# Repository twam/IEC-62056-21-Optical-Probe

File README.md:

IEC-62056-21-Optical-Probe
===

Optical probe for reading out power meters supporting the [IEC 62056-21](https://www.ungelesen.net/protagWork/media/downloads/solar-steuerung/iec62056-21%7Bed1.0%7Den_.pdf) standard via USB.

Infrared part is based on https://wiki.volkszaehler.org/hardware/controllers/ir-schreib-lesekopf-ttl-ausgang.

For the case a ring magnet with Ø 26,75/16 mm and 5 mm height is required, e.g. [this one](https://www.supermagnete.de/eng/ring-magnets-neodymium/ring-magnet-26.75mm-16mm-5mm_R-27-16-05-N).

### JLCPCB

PCBs can be ordered fully-assembled (besides the IR-LED and Photodiode) from [JLCPCB](https://jlcpcb.com/DDE). Required files are
[IEC-62056-21-Optical-Probe_cpl_jlc.csv](Gerber/IEC-62056-21-Optical-Probe_cpl_jlc.csv), [IEC-62056-21-Optical-Probe_bom_jlc.csv](Gerber/IEC-62056-21-Optical-Probe_bom_jlc.csv) and
[IEC-62056-21-Optical-Probe.zip](IEC-62056-21-Optical-Probe.zip).

## License

[![CC BY-SA 4.0][cc-by-sa-shield]][cc-by-sa]

This work is licensed under a [Creative Commons Attribution-NonCommercial-ShareAlike 4.0 International License][cc-by-sa].

[![CC BY-SA 4.0][cc-by-sa-image]][cc-by-sa]

[cc-by-sa]: http://creativecommons.org/licenses/by-nc-sa/4.0/
[cc-by-sa-image]: https://licensebuttons.net/l/by-nc-sa/4.0/88x31.png
[cc-by-sa-shield]: https://img.shields.io/badge/License-CC%20BY--NC--SA%204.0-lightgrey.svg

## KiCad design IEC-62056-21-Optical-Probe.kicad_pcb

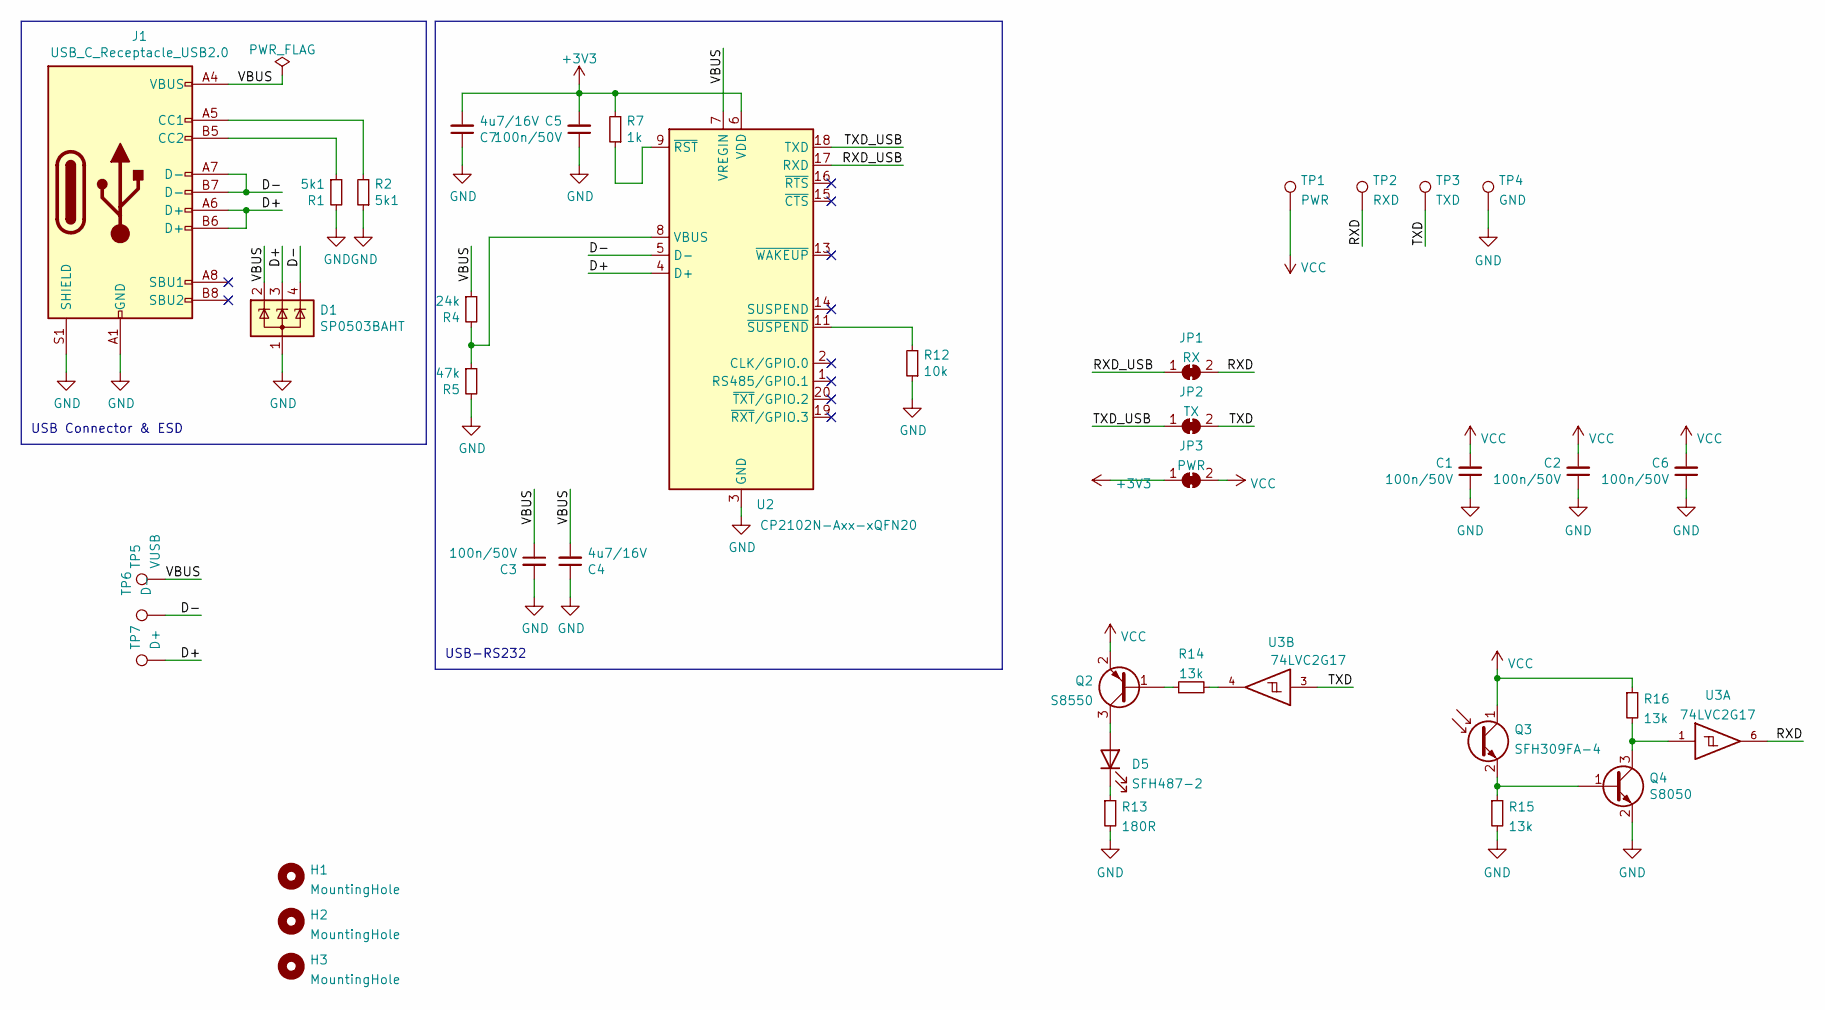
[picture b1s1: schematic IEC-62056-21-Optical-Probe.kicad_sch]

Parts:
C1, C2, C3, C5, C6: 100n/50V; C_0603_1608Metric; LCSC C14663
C4, C7: 4u7/16V; C_0603_1608Metric; LCSC C19666
D1: SP0503BAHT; SOT-143; LCSC C7074
D5: SFH487-2; LED_D3.0mm_IRBlack
H1, H2, H3: MountingHole; MountingHole_JLCPCB
J1: USB_C_Receptacle_USB2.0; USB_C_Receptacle_XKB_U262-16XN-4BVC11; LCSC C165948
JP1: RX; SolderJumper-2_P1.3mm_Bridged_RoundedPad1.0x1.5mm
JP2: TX; SolderJumper-2_P1.3mm_Bridged_RoundedPad1.0x1.5mm
JP3: PWR; SolderJumper-2_P1.3mm_Bridged_RoundedPad1.0x1.5mm
Q2: S8550; SOT-23; LCSC C105432
Q3: SFH309FA-4; LED_D3.0mm_Clear
Q4: S8050; SOT-23; LCSC C2146
R1, R2: 5k1; R_0603_1608Metric; LCSC C23186
R4: 24k; R_0603_1608Metric; LCSC C23352
R5: 47k; R_0603_1608Metric; LCSC C25819
R7: 1k; R_0603_1608Metric; LCSC C21190
R12: 10k; R_0603_1608Metric; LCSC C25804
R13: 180R; R_0603_1608Metric; LCSC C22828
R14, R15, R16: 13k; R_0603_1608Metric; LCSC C22797
TP1: PWR; TestPoint_Pad_2.0x2.0mm
TP2: RXD; TestPoint_Pad_2.0x2.0mm
TP3: TXD; TestPoint_Pad_2.0x2.0mm
TP4: GND; TestPoint_Pad_2.0x2.0mm
TP5: VUSB; TestPoint_Pad_2.0x2.0mm
TP6: D-; TestPoint_Pad_2.0x2.0mm
TP7: D+; TestPoint_Pad_2.0x2.0mm
U2: CP2102N-Axx-xQFN20; SiliconLabs_QFN-20-1EP_3x3mm_P0.5mm_EP1.8x1.8mm; LCSC C969913
U3: 74LVC2G17; SC-74-6_1.5x2.9mm_P0.95mm; LCSC C513289

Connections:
+3V3: C5.2, C7.2, JP3.1 (A), R7.2, U2.6 (VDD)
/D+: D1.3 (K), J1.A6 (D+), J1.B6 (D+), TP7.1, U2.4 (D+)
/D-: D1.4 (K), J1.A7 (D-), J1.B7 (D-), TP6.1, U2.5 (D-)
/RXD: JP1.2 (B), TP2.1, U3.6
/RXD_USB: JP1.1 (A), U2.17 (RXD)
/TXD: JP2.2 (B), TP3.1, U3.3
/TXD_USB: JP2.1 (A), U2.18 (TXD)
/VBUS: C3.1, C4.2, D1.2 (K), J1.A4 (VBUS), J1.A9 (VBUS), J1.B4 (VBUS), J1.B9 (VBUS), R4.1, TP5.1, U2.7 (VREGIN)
GND: C1.1, C2.1, C3.2, C4.1, C5.1, C6.1, C7.1, D1.1 (A), J1.A1 (GND), J1.A12 (GND), J1.B1 (GND), J1.B12 (GND), J1.S1 (SHIELD), Q4.2 (E), R1.2, R2.1, R5.2, R12.1, R13.2, R15.2, TP4.1, U2.3 (GND), U2.12 (GND), U2.21 (GND), U3.2 (GND)
unnamed: D5.1 (K), R13.1
unnamed: D5.2 (A), Q2.3 (C)
unnamed: J1.A5 (CC1), R2.2
unnamed: J1.B5 (CC2), R1.1
unnamed: Q2.1 (B), R14.1
unnamed: Q3.2 (E), Q4.1 (B), R15.1
unnamed: Q4.3 (C), R16.2, U3.1
unnamed: R4.2, R5.1, U2.8 (VBUS)
unnamed: R7.1, U2.9 (~RST)
unnamed: R12.2, U2.11 (~SUSPEND)
unnamed: R14.2, U3.4
VCC: C1.2, C2.2, C6.2, JP3.2 (B), Q2.2 (E), Q3.1 (C), R16.1, TP1.1, U3.5 (VCC)

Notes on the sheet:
USB Connector & ESD
USB-RS232

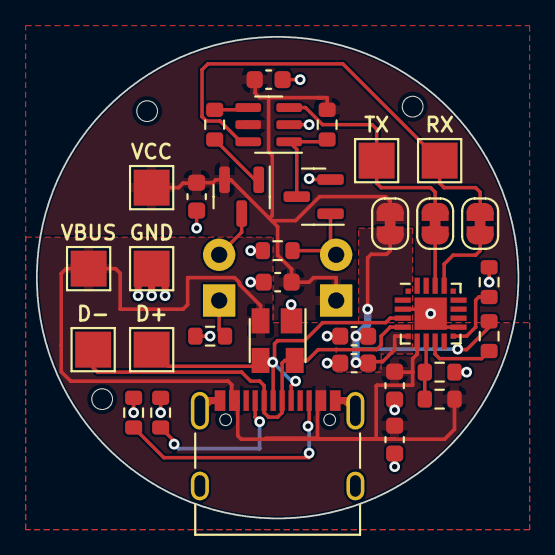
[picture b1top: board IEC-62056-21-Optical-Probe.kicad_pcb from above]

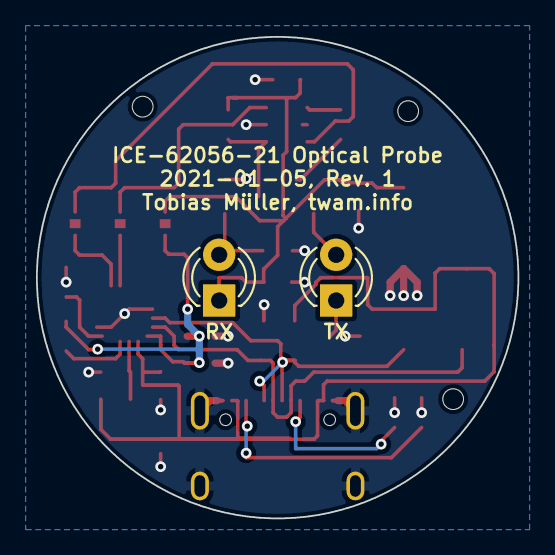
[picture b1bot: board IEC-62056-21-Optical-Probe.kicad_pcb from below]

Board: 2 copper layers, 26.8 x 26.8 mm, 38 parts (2 on the bottom side), 21 nets.

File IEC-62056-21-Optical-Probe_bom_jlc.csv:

"Comment","Designator","Footprint","LCSC Part #"
"100n/50V","C1,C2,C3,C5,C6","C_0603_1608Metric","C14663"
"4u7/16V","C4,C7","C_0603_1608Metric","C19666"
"SP0503BAHT","D1","SOT-143","C7074"
"USB_C_Receptacle_USB2.0","J1","USB_C_Receptacle_XKB_U262-16XN-4BVC11","C165948"
"S8550","Q2","SOT-23","C105432"
"S8050","Q4","SOT-23","C2146"
"5k1","R1,R2","R_0603_1608Metric","C23186"
"24k","R4","R_0603_1608Metric","C23352"
"47k","R5","R_0603_1608Metric","C25819"
"1k","R7","R_0603_1608Metric","C21190"
"10k","R12","R_0603_1608Metric","C25804"
"180R","R13","R_0603_1608Metric","C22828"
"13k","R14,R15,R16","R_0603_1608Metric","C22797"
"CP2102N-Axx-xQFN20","U2","SiliconLabs_QFN-20-1EP_3x3mm_P0.5mm_EP1.8x1.8mm","C969913"
"74LVC2G17","U3","SC-74-6_1.5x2.9mm_P0.95mm","C513289"

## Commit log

2022-01-05 Initial revision
2022-01-07 Move JLCPCB files to Gerber
2022-01-07 Add .gitignore
2022-01-22 Add Case
2025-06-26 Add F3D version of case
2025-06-26 Add images
2025-06-26 Add information about ring magnet
